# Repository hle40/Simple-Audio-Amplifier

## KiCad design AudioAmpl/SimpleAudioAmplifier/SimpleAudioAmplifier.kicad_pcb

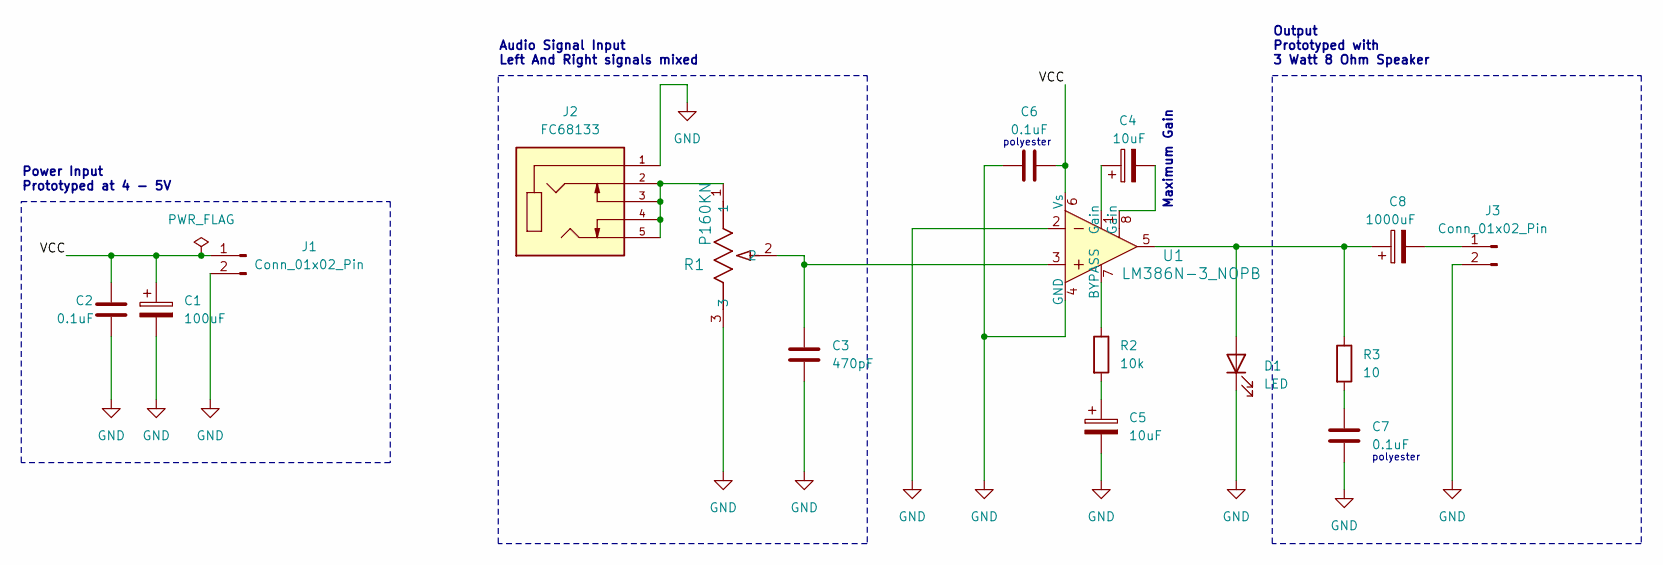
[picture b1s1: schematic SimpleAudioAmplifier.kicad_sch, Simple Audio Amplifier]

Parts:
C1: 100uF; CP_Radial_D7.5mm_P2.50mm
C2, C6, C7: 0.1uF; C_Disc_D3.0mm_W1.6mm_P2.50mm
C3: 470pF; C_Disc_D3.0mm_W1.6mm_P2.50mm
C4, C5: 10uF; CP_Radial_D7.5mm_P2.50mm
C8: 1000uF; CP_Radial_D7.5mm_P2.50mm
D1: LED; LED_D5.0mm
J1, J3: Conn_01x02_Pin; PinHeader_1x02_P2.00mm_Vertical
J2: FC68133; CLIFF_FC68133; PARTREV 5
R1: P160KN; POT_P160KN_F20_TTE
R2: 10k; R_Axial_DIN0204_L3.6mm_D1.6mm_P7.62mm_Horizontal
R3: 10; R_Axial_DIN0204_L3.6mm_D1.6mm_P7.62mm_Horizontal
U1: LM386N-3_NOPB; DIP-8_W7.62mm; MPN LM386N-3/NOPB; Digi-Key_PN 296-43959-5-ND

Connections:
/VCC: C1.1, C2.1, C6.2, J1.1, U1.6 (Vs)
GND: C1.2, C2.2, C3.2, C5.2, C6.1, C7.1, D1.1 (K), J1.2, J2.1, J3.2, R1.3, U1.2, U1.4 (GND)
unnamed: C3.1, R1.2, U1.3
unnamed: C4.1, U1.1 (Gain)
unnamed: C4.2, U1.8 (Gain)
unnamed: C5.1, R2.2
unnamed: C7.2, R3.2
unnamed: C8.1, D1.2 (A), R3.1, U1.5
unnamed: J2.2, J2.3, J2.4, J2.5, R1.1
unnamed: C8.2, J3.1
unnamed: R2.1, U1.7 (BYPASS)

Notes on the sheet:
polyester
Maximum Gain
Output Prototyped with 3 Watt 8 Ohm Speaker
Power Input Prototyped at 4 - 5V
Audio Signal Input Left And Right signals mixed

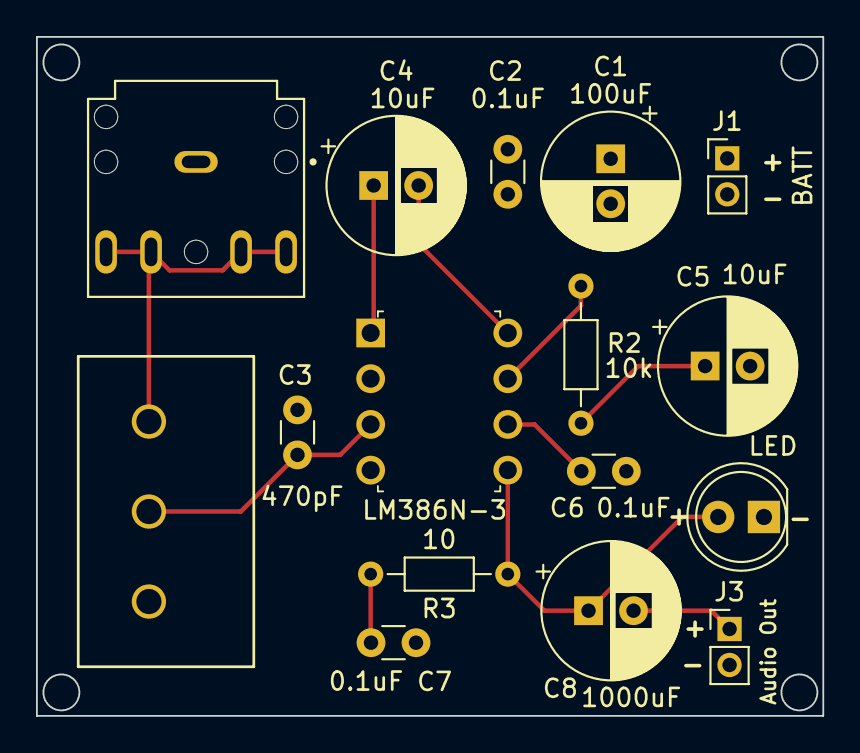
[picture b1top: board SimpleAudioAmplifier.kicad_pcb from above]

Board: 2 copper layers, 43.7 x 37.7 mm, 16 parts (0 on the bottom side), 11 nets.
